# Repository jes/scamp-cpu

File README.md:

# SCAMP CPU

SCAMP is my homebrew 16-bit CPU. It stands for something like "Simple Computing and Arithmetic Microcoded Processor".

The CPU is very primitive. It doesn't support interrupts, and has no MMU, and no concept of privilege levels. It currently runs
at 1 MHz, above that the CompactFlash interface falls over. It runs a homebrew operating system, with a homebrew
programming language and compiler, and can self-host the kernel and all of the system utilities.
The environment tastes a bit like an early Unix, but works like CP/M. I used the computer to complete
almost all of [Advent of Code 2021](https://adventofcode.com/2021/).

My Advent of Code solutions are here: https://github.com/jes/aoc2021

I have some blog posts here: https://incoherency.co.uk/blog/tags/cpu.html and a web-based emulator available here: https://incoherency.co.uk/scamp/

Here are some pictures:

And here's a video with some explanation and an example session on real hardware:

## Architecture

It is a 16-bit CPU. The bus is 16-bit, registers are 16-bit, addresses are 16-bit, and memory contents are
16-bit. The upper 8 bits of an instruction select the opcode, and the lower 8 bits are available
for small immediate values. There is no support for: cache, interrupts, virtual memory, DMA, privilege rings,
floating point, and ~anything else that is not strictly necessary.

Here is a diagram of the architecture:

For more information, see [doc/UCODE.md](doc/UCODE.md) and [doc/ISA.md](doc/ISA.md).

## Try it out

The easiest way to try it out is to use the web-based emulator at https://incoherency.co.uk/scamp/

If you want to run it locally, first you'll need to build everything. Try `make -j` in the root directory of this
repository. It probably won't work on the first attempt because it works with multiple different Makefiles that have
annoying dependencies. Just run `make -j` twice or three times. If that doesn't do the trick, run `make` in `sys/` first, and then run
it in `.`. Once you get to the point that it is only complaining about `emcc`, you're done, unless you also
want to build the web-based emulator.

Having built everything, you can go into `kernel/` and start it in the emulator with `./run`:

    ~/scamp-cpu/kernel $ ./run
    make: 'os.disk' is up to date.
    SCAMP boot...
    .......................................................OK
    starting kernel...
    loading init...
          ____   ____    _    __  __ ____   __
         / ___| / ___|  / \  |  \/  |  _ \ / /__  ___
         \___ \| |     / _ \ | |\/| | |_) / / _ \/ __|
          ___) | |___ / ___ \| |  | |  __/ / (_) \__ \
         |____/ \____/_/   \_\_|  |_|_| /_/ \___/|___/

    $

If you know how to use Unix you'll probably understand how to use it. If you know how to use CP/M you'll probably
understand how it works.

If you want, you can write SLANG programs using `kilo` and compile them with `slc`. You've probably never written
SLANG before. You can learn how to use it by reading programs under `/src` (or `sys/` in the repo). It's mostly
like C but with fewer features and less safety.

## How it's made

I did these tasks, but working on several steps at a time (i.e. I didn't wait until after I had built the entire
computer before thinking about microcode or the operating system):

1. Create the CPU in Verilog, with a testbench for each part.
2. Replace the raw Verilog with Verilog that only uses 74xx-compatible primitives
   (e.g. https://github.com/TimRudy/ice-chips-verilog), but still passes the testbenches.
3. Convert the 74xx-Verilog into KiCad schematics (by hand).
4. Order the PCBs and components, solder up the PCBs, build a card cage, build a wooden case.
5. Settle on the instruction set and write the microcode (see [doc/table.html](doc/table.html), available online at https://incoherency.co.uk/interest/table.html).
5. Write a bootloader, kernel, shell, text editor, compiler, and various system utilities.

## Next steps

I suspect the computer will never be "finished", but some things I still want to work on are:

#### Hardware

 - [ ] build a hardware multiplication card (and maybe division?)
 - [ ] build a hardware RNG

#### Low-level software

 - [ ] make library blob self-hosting (compile within SCAMP/os)
 - [ ] write an strace-like debugging tool
 - [ ] write a DDT-like debugging tool
 - [ ] better facility for memory profiling (mainly to stop kilo and asm from running out of memory on large inputs)
 - [ ] atexit()
 - [ ] static initialisation of globals from constants (e.g. `var x = 5` at global scope should not take any code to initialise)
 - [ ] "const" variables (e.g. `const x = 5` should lead to `x` being replaced with the constant value `5` where possible)

#### Other software

 - [ ] write a big-fixed-point arithmetic library
 - [ ] fixed-point mathematics: pow,tan,asin,acos,atan,atan2
 - [ ] write a FORTH implementation (should it run on bare metal or under SCAMP/os?)
 - [ ] write a Z-machine interpreter and port some text adventures
 - [ ] write some games (pong? breakout? tetris?)

If you happen to want to work on any of the above, I'd be happy to help you!

## Resources

I thoroughly recommend the Nand2Tetris course. https://nand2tetris.org/

If you want to do the exercises from Nand2Tetris without learning what a hardware-description language
is, and without going through all the lectures, you can play https://nandgame.com/

Ben Eater's [videos on 8-bit CPU design](https://www.youtube.com/watch?v=HyznrdDSSGM&list=PLowKtXNTBypGqImE405J2565dvjafglHU) are excellent and heavily influenced
the design of my CPU.

I found the [YouTube playlist](https://www.youtube.com/playlist?list=PLOech0kWpH8-njQpmSNGSiQBPUvl8v3IM) for Nicolas Laurent's [compiler class](https://norswap.com/compilers/) quite helpful
in writing the parser for the compiler.

The [Build Your Own Text Editor](https://viewsourcecode.org/snaptoken/kilo/) is a fantastic tutorial that walks you through implementing
[antirez](https://github.com/antirez)'s [kilo](https://github.com/antirez/kilo) editor.

[Balazs Markus](https://github.com/bazsimarkus)'s [8250 UART example](https://github.com/bazsimarkus/Simple-8250-UART-System-with-Arduino) is helpful.

Daniel Tufvesson has a post that is a good starting point for understanding the [8-bit CompactFlash interface](http://www.waveguide.se/?article=8-bit-compact-flash-interface).

[PickledDog](https://github.com/PickledDog) has a description of an [improvement to the RC2014 CompactFlash card](https://github.com/PickledDog/rc-cfcard) that might be helpful. Also [Bill Shen's comment on the RC2014 mailing list](https://groups.google.com/g/rc2014-z80/c/LmvGa6PZNhQ/m/H8jrbp86AQAJ).

Michał Cierniak has a good blog post about [CompactFlash + 8255 interface card](https://ciernioo.wordpress.com/2015/02/10/compact-flash-8255-interface-card/) with lots
of detail on how his CompactFlash interface works.

[James Sharman](https://www.youtube.com/c/weirdboyjim) is building an interesting 8-bit pipelined CPU, and has good videos with lots of explanation on how it works.

SCAMP is featured on the [Homebrew CPU ring](https://www.homebrewcpuring.org/) which also features many other interesting homebrew CPU designs.

## Contact

You can email me on [james@incoherency.co.uk](mailto:james@incoherency.co.uk)
or read my blog: [https://incoherency.co.uk/].

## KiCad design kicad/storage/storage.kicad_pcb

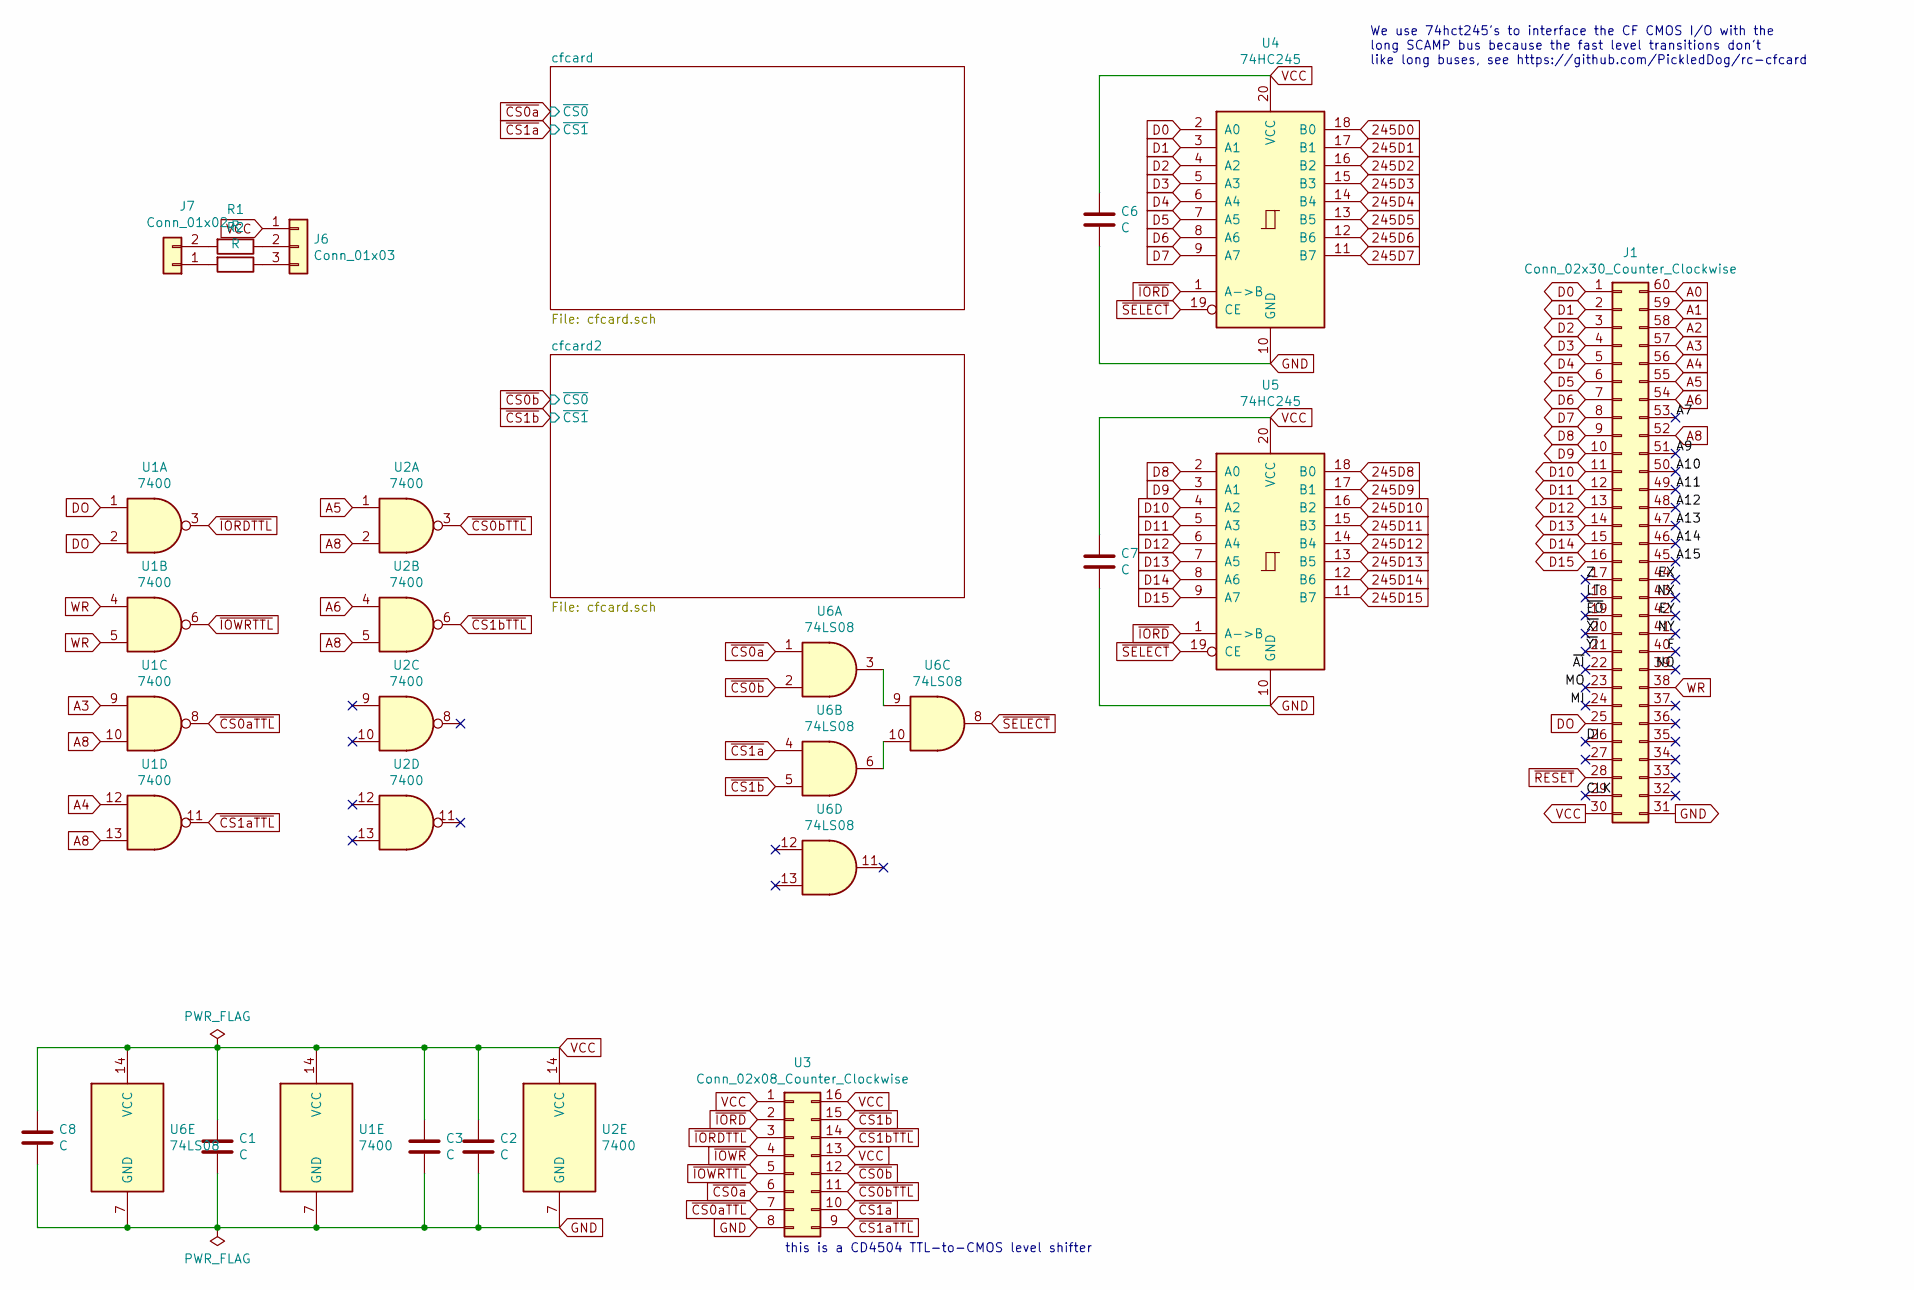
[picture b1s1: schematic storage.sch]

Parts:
C1, C2, C3, C6, C7, C8: C; C_Disc_D6.0mm_W2.5mm_P5.00mm
J1: Conn_02x30_Counter_Clockwise; PinSocket_2x30_P2.54mm_Horizontal
J6: Conn_01x03; PinHeader_1x03_P2.54mm_Vertical
J7: Conn_01x02; PinHeader_1x02_P2.54mm_Vertical
R1, R2: R; R_Axial_DIN0207_L6.3mm_D2.5mm_P10.16mm_Horizontal
U1, U2: 7400; DIP-14_W7.62mm_Socket
U3: Conn_02x08_Counter_Clockwise; DIP-16_W7.62mm_Socket
U4, U5: 74HC245; DIP-20_W7.62mm_Socket
U6: 74LS08; DIP-14_W7.62mm_Socket

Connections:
245D0: U4.18 (B0); also elsewhere on the board
245D1: U4.17 (B1); also elsewhere on the board
245D2: U4.16 (B2); also elsewhere on the board
245D3: U4.15 (B3); also elsewhere on the board
245D4: U4.14 (B4); also elsewhere on the board
245D5: U4.13 (B5); also elsewhere on the board
245D6: U4.12 (B6); also elsewhere on the board
245D7: U4.11 (B7); also elsewhere on the board
245D8: U5.18 (B0); also elsewhere on the board
245D9: U5.17 (B1); also elsewhere on the board
245D10: U5.16 (B2); also elsewhere on the board
245D11: U5.15 (B3); also elsewhere on the board
245D12: U5.14 (B4); also elsewhere on the board
245D13: U5.13 (B5); also elsewhere on the board
245D14: U5.12 (B6); also elsewhere on the board
245D15: U5.11 (B7); also elsewhere on the board
/A7: J1.53
/A9: J1.51
/A10: J1.50
/A11: J1.49
/A12: J1.48
/A13: J1.47
/A14: J1.46
/A15: J1.45
/CLK: J1.29
/DI: J1.26
/EX: J1.44
/EY: J1.42
/F: J1.40
/LT: J1.18
/MI: J1.24
/MO: J1.23
/NO: J1.39
/NX: J1.43
/NY: J1.41
/Z: J1.17
/~AI~: J1.22
/~EO~: J1.19
/~XI~: J1.20
/~YI~: J1.21
A0: J1.60; also elsewhere on the board
A1: J1.59; also elsewhere on the board
A2: J1.58; also elsewhere on the board
A3: J1.57, U1.9
A4: J1.56, U1.12
A5: J1.55, U2.1
A6: J1.54, U2.4
A8: J1.52, U1.10, U1.13, U2.2, U2.5
D0: J1.1, U4.2 (A0)
D1: J1.2, U4.3 (A1)
D2: J1.3, U4.4 (A2)
D3: J1.4, U4.5 (A3)
D4: J1.5, U4.6 (A4)
D5: J1.6, U4.7 (A5)
D6: J1.7, U4.8 (A6)
D7: J1.8, U4.9 (A7)
D8: J1.9, U5.2 (A0)
D9: J1.10, U5.3 (A1)
D10: J1.11, U5.4 (A2)
D11: J1.12, U5.5 (A3)
D12: J1.13, U5.6 (A4)
D13: J1.14, U5.7 (A5)
D14: J1.15, U5.8 (A6)
D15: J1.16, U5.9 (A7)
DO: J1.25, U1.1, U1.2
GND: C1.2, C2.2, C3.2, C6.2, C7.2, C8.2, J1.31, U1.7 (GND), U2.7 (GND), U3.8, U4.10 (GND), U5.10 (GND), U6.7 (GND); also elsewhere on the board
unnamed: J6.2, R1.1
unnamed: J6.3, R2.1
unnamed: J7.1, R2.2
unnamed: J7.2, R1.2
unnamed: U6.3, U6.9
unnamed: U6.6, U6.10
VCC: C1.1, C2.1, C3.1, C6.1, C7.1, C8.1, J1.30, J6.1, U1.14 (VCC), U2.14 (VCC), U3.1, U3.13, U3.16, U4.20 (VCC), U5.20 (VCC), U6.14 (VCC); also elsewhere on the board
WR: J1.38, U1.4, U1.5
~CS0aTTL~: U1.8, U3.7
~CS0a~: U3.6, U6.1; also elsewhere on the board
~CS0bTTL~: U2.3, U3.11
~CS0b~: U3.12, U6.2; also elsewhere on the board
~CS1aTTL~: U1.11, U3.9
~CS1a~: U3.10, U6.4; also elsewhere on the board
~CS1bTTL~: U2.6, U3.14
~CS1b~: U3.15, U6.5; also elsewhere on the board
~IORDTTL~: U1.3, U3.3
~IORD~: U3.2, U4.1 (A->B), U5.1 (A->B); also elsewhere on the board
~IOWRTTL~: U1.6, U3.5
~IOWR~: U3.4; also elsewhere on the board
~RESET~: J1.28; also elsewhere on the board
~SELECT~: U4.19 (CE), U5.19 (CE), U6.8

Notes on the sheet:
this is a CD4504 TTL-to-CMOS level shifter
We use 74hct245's to interface the CF CMOS I/O with the long SCAMP bus because the fast level transitions don't like long buses, see https://github.com/PickledDog/rc-cfcard

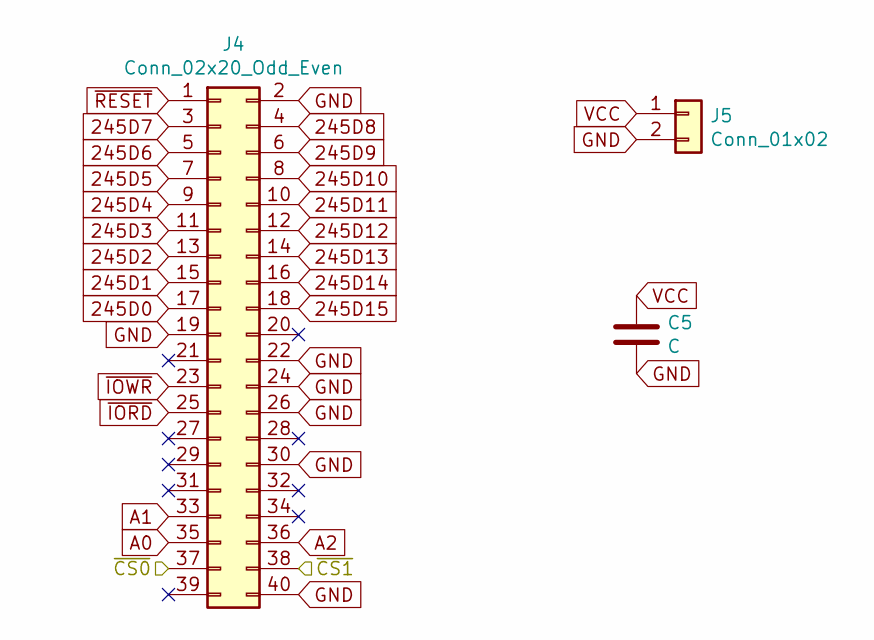
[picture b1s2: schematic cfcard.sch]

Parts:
C4: C; C_Disc_D6.0mm_W2.5mm_P5.00mm
J2: Conn_02x20_Odd_Even; cfcard
J3: Conn_01x02; PinHeader_1x02_P2.54mm_Vertical

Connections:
245D0: J2.17; also elsewhere on the board
245D1: J2.15; also elsewhere on the board
245D2: J2.13; also elsewhere on the board
245D3: J2.11; also elsewhere on the board
245D4: J2.9; also elsewhere on the board
245D5: J2.7; also elsewhere on the board
245D6: J2.5; also elsewhere on the board
245D7: J2.3; also elsewhere on the board
245D8: J2.4; also elsewhere on the board
245D9: J2.6; also elsewhere on the board
245D10: J2.8; also elsewhere on the board
245D11: J2.10; also elsewhere on the board
245D12: J2.12; also elsewhere on the board
245D13: J2.14; also elsewhere on the board
245D14: J2.16; also elsewhere on the board
245D15: J2.18; also elsewhere on the board
A0: J2.35; also elsewhere on the board
A1: J2.33; also elsewhere on the board
A2: J2.36; also elsewhere on the board
GND: C4.2, J2.2, J2.19, J2.22, J2.24, J2.26, J2.30, J2.40, J3.2; also elsewhere on the board
VCC: C4.1, J3.1; also elsewhere on the board
~CS0a~: J2.37; also elsewhere on the board
~CS1a~: J2.38; also elsewhere on the board
~IORD~: J2.25; also elsewhere on the board
~IOWR~: J2.23; also elsewhere on the board
~RESET~: J2.1; also elsewhere on the board

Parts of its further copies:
C5: C; C_Disc_D6.0mm_W2.5mm_P5.00mm
J4: Conn_02x20_Odd_Even; cfcard
J5: Conn_01x02; PinHeader_1x02_P2.54mm_Vertical

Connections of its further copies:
245D0: J4.17; also elsewhere on the board
245D1: J4.15; also elsewhere on the board
245D2: J4.13; also elsewhere on the board
245D3: J4.11; also elsewhere on the board
245D4: J4.9; also elsewhere on the board
245D5: J4.7; also elsewhere on the board
245D6: J4.5; also elsewhere on the board
245D7: J4.3; also elsewhere on the board
245D8: J4.4; also elsewhere on the board
245D9: J4.6; also elsewhere on the board
245D10: J4.8; also elsewhere on the board
245D11: J4.10; also elsewhere on the board
245D12: J4.12; also elsewhere on the board
245D13: J4.14; also elsewhere on the board
245D14: J4.16; also elsewhere on the board
245D15: J4.18; also elsewhere on the board
A0: J4.35; also elsewhere on the board
A1: J4.33; also elsewhere on the board
A2: J4.36; also elsewhere on the board
GND: C5.2, J4.2, J4.19, J4.22, J4.24, J4.26, J4.30, J4.40, J5.2; also elsewhere on the board
VCC: C5.1, J5.1; also elsewhere on the board
~CS0b~: J4.37; also elsewhere on the board
~CS1b~: J4.38; also elsewhere on the board
~IORD~: J4.25; also elsewhere on the board
~IOWR~: J4.23; also elsewhere on the board
~RESET~: J4.1; also elsewhere on the board

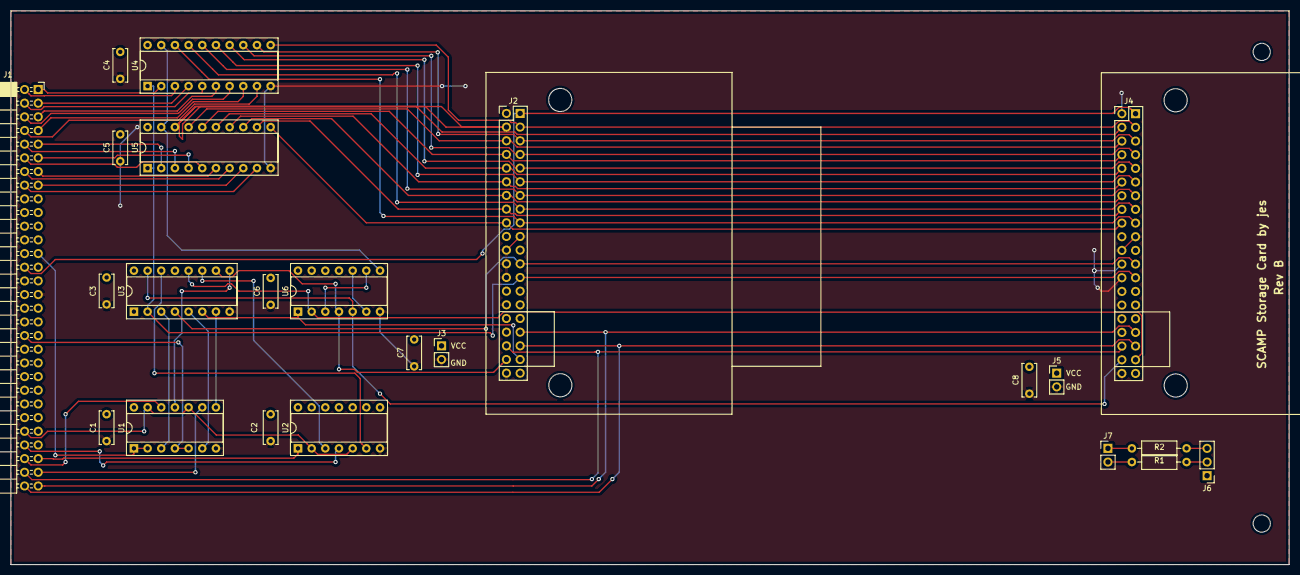
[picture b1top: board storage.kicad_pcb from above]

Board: 2 copper layers, 237.5 x 102.9 mm, 23 parts (0 on the bottom side), 64 nets.

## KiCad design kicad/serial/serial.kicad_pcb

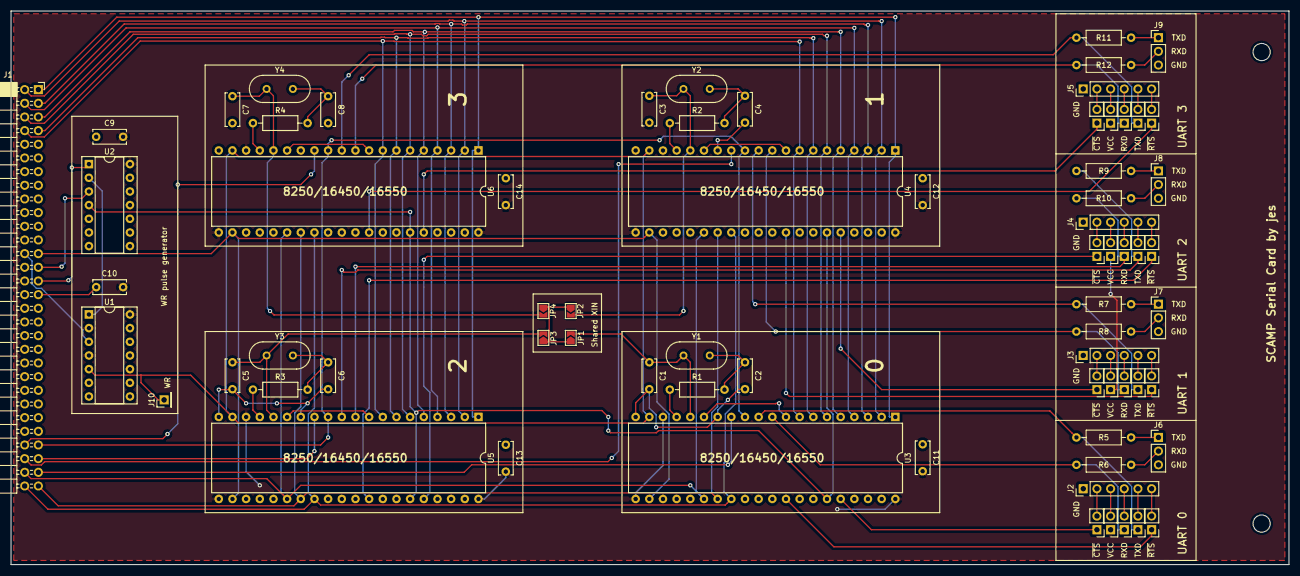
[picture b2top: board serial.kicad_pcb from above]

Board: 2 copper layers, 237.5 x 102.9 mm, 62 parts (0 on the bottom side), 70 nets.

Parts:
C1, C2, C3, C4, C5, C6, C7, C8, C9, C10, C11, C12, C13, C14: C; C_Disc_D6.0mm_W2.5mm_P5.00mm
J1: Conn_02x30_Counter_Clockwise; PinSocket_2x30_P2.54mm_Horizontal
J2, J3, J4, J5: Conn_01x06_Male; PinHeader_1x06_P2.54mm_Vertical
J6, J7, J8, J9: Conn_01x03_Male; PinHeader_1x03_P2.54mm_Vertical
J10: Conn_01x01_Male; PinHeader_1x01_P2.54mm_Vertical
JP1, JP2, JP3, JP4: SolderJumper_2_Open; SolderJumper-2_P1.3mm_Open_TrianglePad1.0x1.5mm
R1, R2, R3, R4, R5, R6, R7, R8, R9, R10, R11, R12: R; R_Axial_DIN0207_L6.3mm_D2.5mm_P10.16mm_Horizontal
RXD: Jumper_NO_Small; PinHeader_1x02_P2.54mm_Vertical
RXD#2, RXD#3, RXD#4: Jumper_NO_Small; PinHeader_1x02_P2.54mm_Vertical
TXD: Jumper_NO_Small; PinHeader_1x02_P2.54mm_Vertical
TXD#2, TXD#3, TXD#4: Jumper_NO_Small; PinHeader_1x02_P2.54mm_Vertical
U1: 74LS74; DIP-14_W7.62mm_Socket
U2: 74LS04; DIP-14_W7.62mm_Socket
U3, U4, U5, U6: 8250; DIP-40_W15.24mm
VCC: Jumper_NO_Small; PinHeader_1x02_P2.54mm_Vertical
VCC#2, VCC#3, VCC#4: Jumper_NO_Small; PinHeader_1x02_P2.54mm_Vertical
Y1, Y2, Y3, Y4: Crystal; Crystal_HC49-U_Vertical

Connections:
/uart8250a/RXD: R6.2, RXD.1, U3.10
/uart8250a/TXD: R5.2, TXD.1, U3.11
/uart8250b/RXD: R8.2, RXD#2.1, U4.10
/uart8250b/TXD: R7.2, TXD#2.1, U4.11
/uart8250c/RXD: R10.2, RXD#3.1, U5.10
/uart8250c/TXD: R9.2, TXD#3.1, U5.11
/uart8250d/RXD: R12.2, RXD#4.1, U6.10
/uart8250d/TXD: R11.2, TXD#4.1, U6.11
A0: J1.60, U3.28, U4.28, U5.28, U6.28
A1: J1.59, U3.27, U4.27, U5.27, U6.27
A2: J1.58, U3.26, U4.26, U5.26, U6.26
A3: J1.57, U3.13
A4: J1.56, U4.13
A5: J1.55, U5.13
A6: J1.54, U6.13
A7: J1.53, U3.12, U4.12, U5.12, U6.12
CLK: J1.29, U2.1
D0: J1.1, U3.1, U4.1, U5.1, U6.1
D1: J1.2, U3.2, U4.2, U5.2, U6.2
D2: J1.3, U3.3, U4.3, U5.3, U6.3
D3: J1.4, U3.4, U4.4, U5.4, U6.4
D4: J1.5, U3.5, U4.5, U5.5, U6.5
D5: J1.6, U3.6, U4.6, U5.6, U6.6
D6: J1.7, U3.7, U4.7, U5.7, U6.7
D7: J1.8, U3.8, U4.8, U5.8, U6.8
DI: J1.26, U1.3
DO: J1.25, U3.22, U4.22, U5.22, U6.22
GND: C1.2, C2.2, C3.2, C4.2, C5.2, C6.2, C7.2, C8.2, C9.2, C10.2, C11.2, C12.2, C13.2, C14.2, J1.31, J2.1, J3.1, J4.1, J5.1, J6.3, J7.3, J8.3, J9.3, U1.7, U2.7, U3.14, U3.20, U3.25, U4.14, U4.20, U4.25, U5.14, U5.20, U5.25, U6.14, U6.20, U6.25
unnamed: C1.1, JP1.2, U3.16, Y1.1
unnamed: C2.1, R1.2, Y1.2
unnamed: C3.1, JP2.2, U4.16, Y2.1
unnamed: C4.1, R2.2, Y2.2
unnamed: C5.1, JP3.2, U5.16, Y3.1
unnamed: C6.1, R3.2, Y3.2
unnamed: C7.1, JP4.2, U6.16, Y4.1
unnamed: C8.1, R4.2, Y4.2
unnamed: J2.3, VCC.2
unnamed: J2.4, RXD.2
unnamed: J2.5, TXD.2
unnamed: J3.3, VCC#2.2
unnamed: J3.4, RXD#2.2
unnamed: J3.5, TXD#2.2
unnamed: J4.3, VCC#3.2
unnamed: J4.4, RXD#3.2
unnamed: J4.5, TXD#3.2
unnamed: J5.3, VCC#4.2
unnamed: J5.4, RXD#4.2
unnamed: J5.5, TXD#4.2
unnamed: J6.1, R5.1
unnamed: J6.2, R6.1
unnamed: J7.1, R7.1
unnamed: J7.2, R8.1
unnamed: J8.1, R9.1
unnamed: J8.2, R10.1
unnamed: J9.1, R11.1
unnamed: J9.2, R12.1
unnamed: R1.1, U3.17
unnamed: R2.1, U4.17
unnamed: R3.1, U5.17
unnamed: R4.1, U6.17
unnamed: U3.9, U3.15
unnamed: U4.9, U4.15
unnamed: U5.9, U5.15
unnamed: U6.9, U6.15
SHAREDXIN: JP1.1, JP2.1, JP3.1, JP4.1
VCC: C9.1, C10.1, C11.1, C12.1, C13.1, C14.1, J1.30, U1.2, U1.4, U1.14, U2.14, U3.18, U3.21, U3.40, U4.18, U4.21, U4.40, U5.18, U5.21, U5.40, U6.18, U6.21, U6.40, VCC.1, VCC#2.1, VCC#3.1, VCC#4.1
WR: J10.1, U1.5, U3.19, U4.19, U5.19, U6.19
inv_CLK: U1.1, U2.2
inv_~RESET: U2.4, U3.35, U4.35, U5.35, U6.35
~RESET: J1.27, U2.3

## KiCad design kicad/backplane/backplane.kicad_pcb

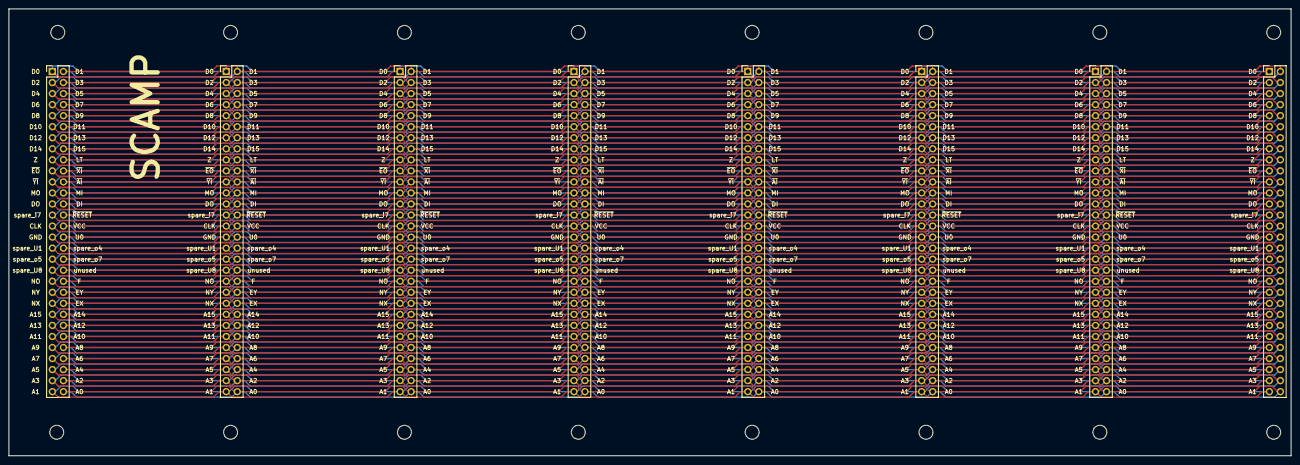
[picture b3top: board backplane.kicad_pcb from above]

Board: 2 copper layers, 295.0 x 102.8 mm, 8 parts (0 on the bottom side), 60 nets.

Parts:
J1, J2, J3, J4, J5, J6, J7, J8: Conn_02x30_Counter_Clockwise; PinHeader_2x30_P2.54mm_Vertical

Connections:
A0: J1.60, J2.60, J3.60, J4.60, J5.60, J6.60, J7.60, J8.60
A1: J1.59, J2.59, J3.59, J4.59, J5.59, J6.59, J7.59, J8.59
A2: J1.58, J2.58, J3.58, J4.58, J5.58, J6.58, J7.58, J8.58
A3: J1.57, J2.57, J3.57, J4.57, J5.57, J6.57, J7.57, J8.57
A4: J1.56, J2.56, J3.56, J4.56, J5.56, J6.56, J7.56, J8.56
A5: J1.55, J2.55, J3.55, J4.55, J5.55, J6.55, J7.55, J8.55
A6: J1.54, J2.54, J3.54, J4.54, J5.54, J6.54, J7.54, J8.54
A7: J1.53, J2.53, J3.53, J4.53, J5.53, J6.53, J7.53, J8.53
A8: J1.52, J2.52, J3.52, J4.52, J5.52, J6.52, J7.52, J8.52
A9: J1.51, J2.51, J3.51, J4.51, J5.51, J6.51, J7.51, J8.51
A10: J1.50, J2.50, J3.50, J4.50, J5.50, J6.50, J7.50, J8.50
A11: J1.49, J2.49, J3.49, J4.49, J5.49, J6.49, J7.49, J8.49
A12: J1.48, J2.48, J3.48, J4.48, J5.48, J6.48, J7.48, J8.48
A13: J1.47, J2.47, J3.47, J4.47, J5.47, J6.47, J7.47, J8.47
A14: J1.46, J2.46, J3.46, J4.46, J5.46, J6.46, J7.46, J8.46
A15: J1.45, J2.45, J3.45, J4.45, J5.45, J6.45, J7.45, J8.45
CLK: J1.29, J2.29, J3.29, J4.29, J5.29, J6.29, J7.29, J8.29
D0: J1.1, J2.1, J3.1, J4.1, J5.1, J6.1, J7.1, J8.1
D1: J1.2, J2.2, J3.2, J4.2, J5.2, J6.2, J7.2, J8.2
D2: J1.3, J2.3, J3.3, J4.3, J5.3, J6.3, J7.3, J8.3
D3: J1.4, J2.4, J3.4, J4.4, J5.4, J6.4, J7.4, J8.4
D4: J1.5, J2.5, J3.5, J4.5, J5.5, J6.5, J7.5, J8.5
D5: J1.6, J2.6, J3.6, J4.6, J5.6, J6.6, J7.6, J8.6
D6: J1.7, J2.7, J3.7, J4.7, J5.7, J6.7, J7.7, J8.7
D7: J1.8, J2.8, J3.8, J4.8, J5.8, J6.8, J7.8, J8.8
D8: J1.9, J2.9, J3.9, J4.9, J5.9, J6.9, J7.9, J8.9
D9: J1.10, J2.10, J3.10, J4.10, J5.10, J6.10, J7.10, J8.10
D10: J1.11, J2.11, J3.11, J4.11, J5.11, J6.11, J7.11, J8.11
D11: J1.12, J2.12, J3.12, J4.12, J5.12, J6.12, J7.12, J8.12
D12: J1.13, J2.13, J3.13, J4.13, J5.13, J6.13, J7.13, J8.13
D13: J1.14, J2.14, J3.14, J4.14, J5.14, J6.14, J7.14, J8.14
D14: J1.15, J2.15, J3.15, J4.15, J5.15, J6.15, J7.15, J8.15
D15: J1.16, J2.16, J3.16, J4.16, J5.16, J6.16, J7.16, J8.16
DI: J1.26, J2.26, J3.26, J4.26, J5.26, J6.26, J7.26, J8.26
DO: J1.25, J2.25, J3.25, J4.25, J5.25, J6.25, J7.25, J8.25
EX: J1.44, J2.44, J3.44, J4.44, J5.44, J6.44, J7.44, J8.44
EY: J1.42, J2.42, J3.42, J4.42, J5.42, J6.42, J7.42, J8.42
F: J1.40, J2.40, J3.40, J4.40, J5.40, J6.40, J7.40, J8.40
GND: J1.31, J2.31, J3.31, J4.31, J5.31, J6.31, J7.31, J8.31
LT: J1.18, J2.18, J3.18, J4.18, J5.18, J6.18, J7.18, J8.18
MI: J1.24, J2.24, J3.24, J4.24, J5.24, J6.24, J7.24, J8.24
MO: J1.23, J2.23, J3.23, J4.23, J5.23, J6.23, J7.23, J8.23
NO: J1.39, J2.39, J3.39, J4.39, J5.39, J6.39, J7.39, J8.39
NX: J1.43, J2.43, J3.43, J4.43, J5.43, J6.43, J7.43, J8.43
NY: J1.41, J2.41, J3.41, J4.41, J5.41, J6.41, J7.41, J8.41
U0: J1.32, J2.32, J3.32, J4.32, J5.32, J6.32, J7.32, J8.32
VCC: J1.30, J2.30, J3.30, J4.30, J5.30, J6.30, J7.30, J8.30
Z: J1.17, J2.17, J3.17, J4.17, J5.17, J6.17, J7.17, J8.17
spare_U1: J1.33, J2.33, J3.33, J4.33, J5.33, J6.33, J7.33, J8.33
spare_U8: J1.37, J2.37, J3.37, J4.37, J5.37, J6.37, J7.37, J8.37
spare_i7: J1.27, J2.27, J3.27, J4.27, J5.27, J6.27, J7.27, J8.27
spare_o4: J1.34, J2.34, J3.34, J4.34, J5.34, J6.34, J7.34, J8.34
spare_o5: J1.35, J2.35, J3.35, J4.35, J5.35, J6.35, J7.35, J8.35
spare_o7: J1.36, J2.36, J3.36, J4.36, J5.36, J6.36, J7.36, J8.36
unused: J1.38, J2.38, J3.38, J4.38, J5.38, J6.38, J7.38, J8.38
~AI~: J1.22, J2.22, J3.22, J4.22, J5.22, J6.22, J7.22, J8.22
~EO~: J1.19, J2.19, J3.19, J4.19, J5.19, J6.19, J7.19, J8.19
~RESET~: J1.28, J2.28, J3.28, J4.28, J5.28, J6.28, J7.28, J8.28
~XI~: J1.20, J2.20, J3.20, J4.20, J5.20, J6.20, J7.20, J8.20
~YI~: J1.21, J2.21, J3.21, J4.21, J5.21, J6.21, J7.21, J8.21

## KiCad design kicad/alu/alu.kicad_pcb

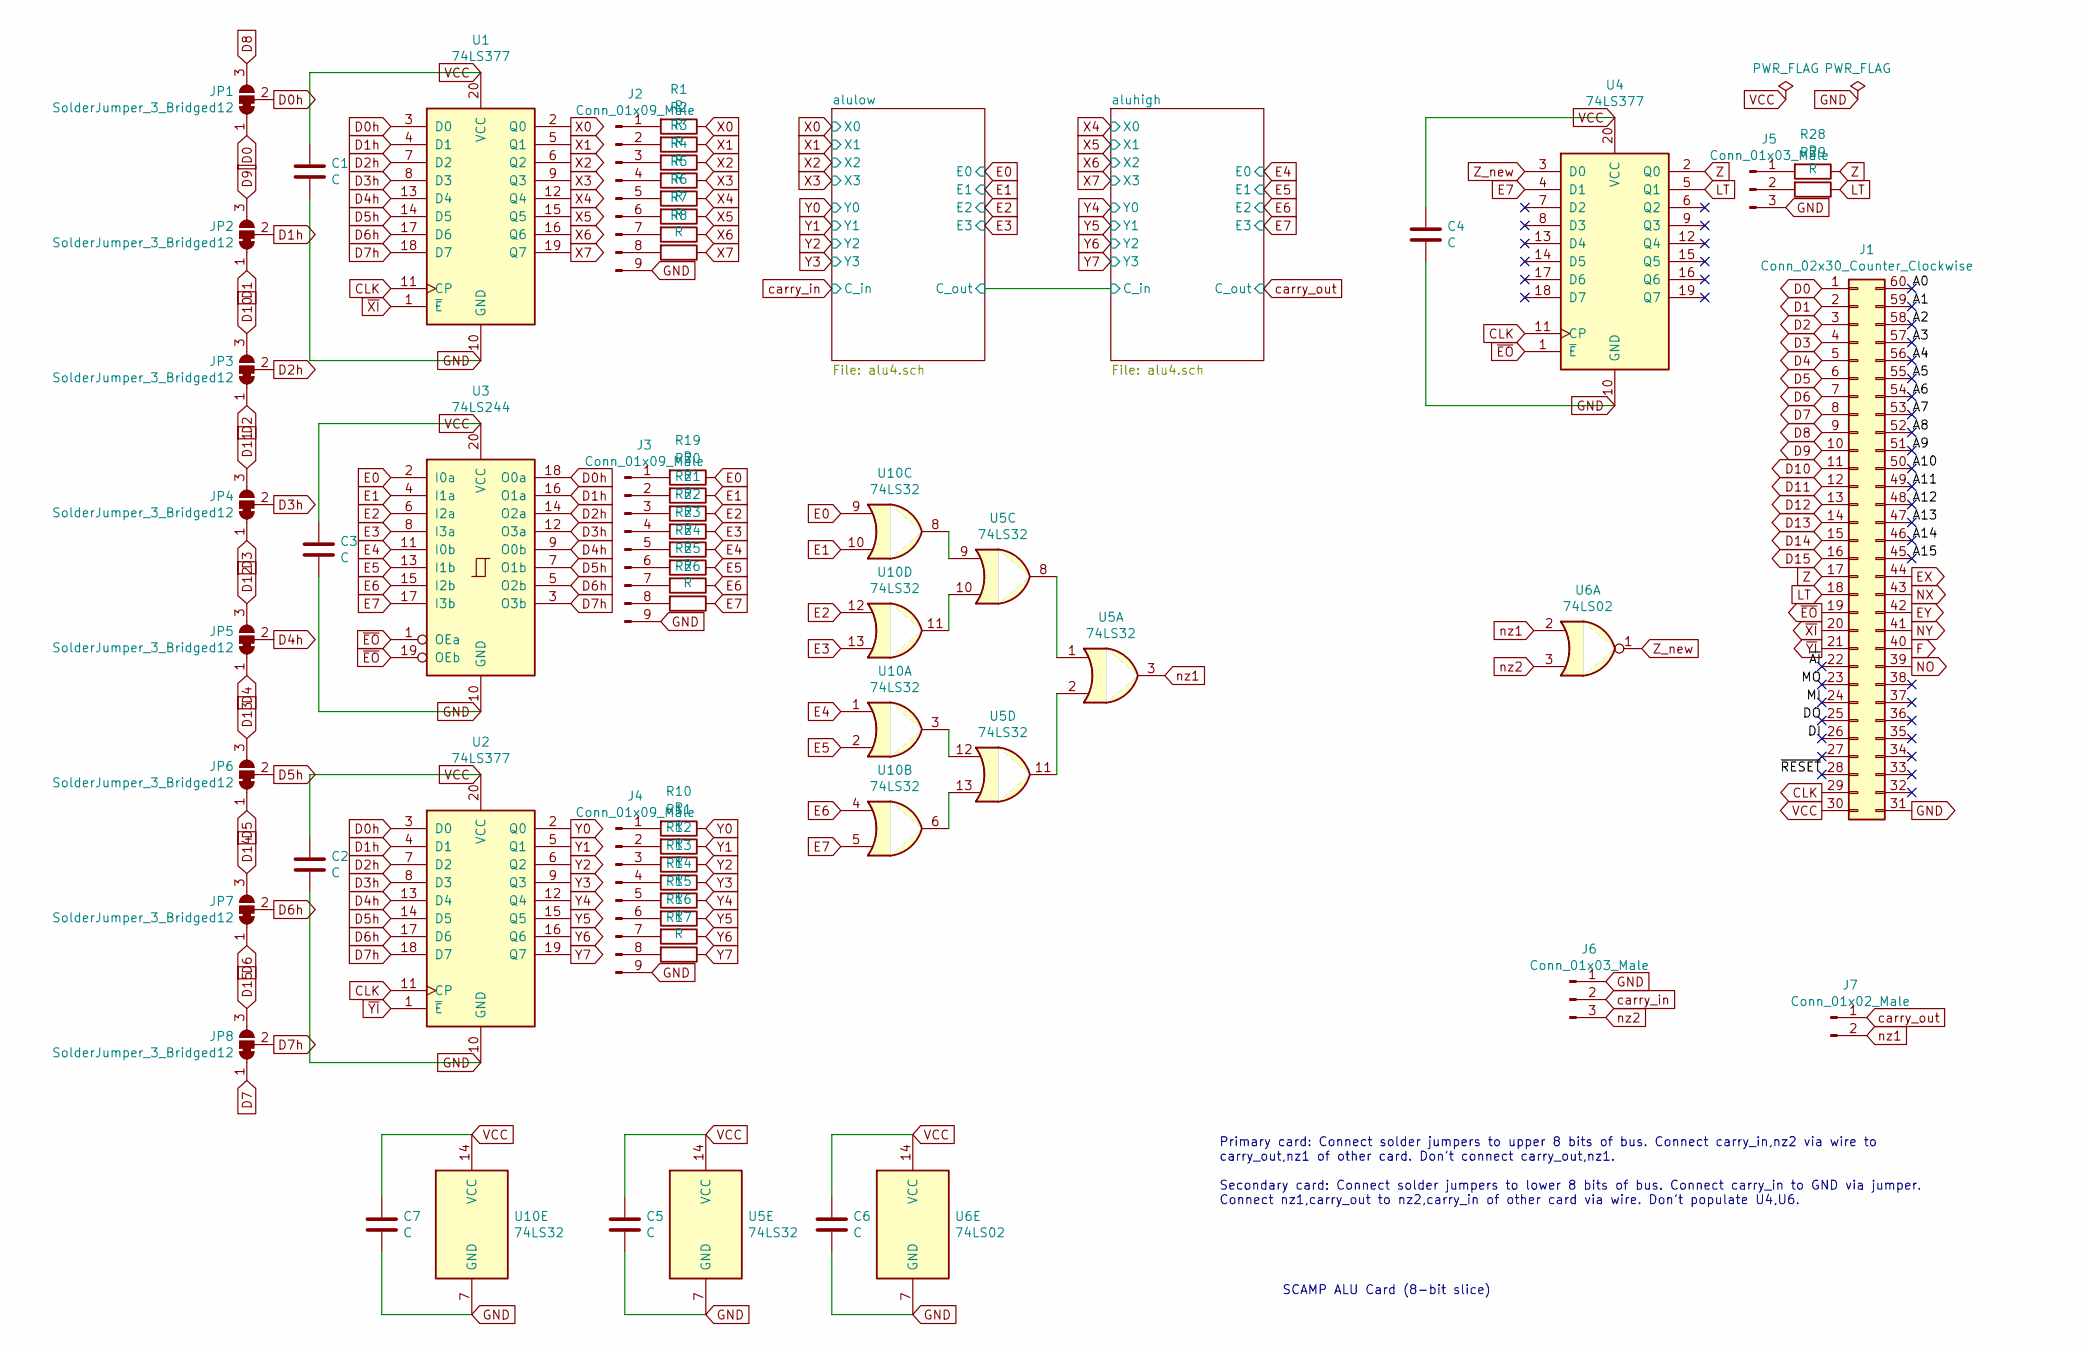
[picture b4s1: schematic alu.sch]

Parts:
C1, C2, C3, C4, C5, C6, C7: C; C_Disc_D5.0mm_W2.5mm_P2.50mm
J1: Conn_02x30_Counter_Clockwise; PinSocket_2x30_P2.54mm_Horizontal
J2, J3, J4: Conn_01x09_Male; PinHeader_1x09_P2.54mm_Vertical
J5, J6: Conn_01x03_Male; PinHeader_1x03_P2.54mm_Vertical
J7: Conn_01x02_Male; PinHeader_1x02_P2.54mm_Vertical
JP1, JP2, JP3, JP4, JP5, JP6, JP7, JP8: SolderJumper_3_Bridged12; SolderJumper-3_P1.3mm_Open_Pad1.0x1.5mm
R1, R2, R3, R4, R5, R6, R7, R8, R10, R11, R12, R13, R14, R15, R16, R17, R19, R20, R21, R22, R23, R24, R25, R26, R28, R29: R; R_Axial_DIN0207_L6.3mm_D2.5mm_P7.62mm_Horizontal
U1, U2, U4: 74LS377; DIP-20_W7.62mm_Socket
U3: 74LS244; DIP-20_W7.62mm_Socket
U5, U10: 74LS32; DIP-14_W7.62mm_Socket
U6: 74LS02; DIP-14_W7.62mm_Socket

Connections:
/A0: J1.60
/A1: J1.59
/A2: J1.58
/A3: J1.57
/A4: J1.56
/A5: J1.55
/A6: J1.54
/A7: J1.53
/A8: J1.52
/A9: J1.51
/A10: J1.50
/A11: J1.49
/A12: J1.48
/A13: J1.47
/A14: J1.46
/A15: J1.45
/DI: J1.26
/DO: J1.25
/MI: J1.24
/MO: J1.23
/~AI~: J1.22
/~RESET~: J1.28
CLK: J1.29, U1.11 (CP), U2.11 (CP), U4.11 (CP)
D0: J1.1, JP1.1 (A)
D0h: JP1.2 (C), U1.3 (D0), U2.3 (D0), U3.18 (O0a)
D1: J1.2, JP2.1 (A)
D1h: JP2.2 (C), U1.4 (D1), U2.4 (D1), U3.16 (O1a)
D2: J1.3, JP3.1 (A)
D2h: JP3.2 (C), U1.7 (D2), U2.7 (D2), U3.14 (O2a)
D3: J1.4, JP4.1 (A)
D3h: JP4.2 (C), U1.8 (D3), U2.8 (D3), U3.12 (O3a)
D4: J1.5, JP5.1 (A)
D4h: JP5.2 (C), U1.13 (D4), U2.13 (D4), U3.9 (O0b)
D5: J1.6, JP6.1 (A)
D5h: JP6.2 (C), U1.14 (D5), U2.14 (D5), U3.7 (O1b)
D6: J1.7, JP7.1 (A)
D6h: JP7.2 (C), U1.17 (D6), U2.17 (D6), U3.5 (O2b)
D7: J1.8, JP8.1 (A)
D7h: JP8.2 (C), U1.18 (D7), U2.18 (D7), U3.3 (O3b)
D8: J1.9, JP1.3 (B)
D9: J1.10, JP2.3 (B)
D10: J1.11, JP3.3 (B)
D11: J1.12, JP4.3 (B)
D12: J1.13, JP5.3 (B)
D13: J1.14, JP6.3 (B)
D14: J1.15, JP7.3 (B)
D15: J1.16, JP8.3 (B)
E0: R19.1, U3.2 (I0a), U10.9; also elsewhere on the board
E1: R20.1, U3.4 (I1a), U10.10; also elsewhere on the board
E2: R21.1, U3.6 (I2a), U10.12; also elsewhere on the board
E3: R22.1, U3.8 (I3a), U10.13; also elsewhere on the board
E4: R23.1, U3.11 (I0b), U10.1; also elsewhere on the board
E5: R24.1, U3.13 (I1b), U10.2; also elsewhere on the board
E6: R25.1, U3.15 (I2b), U10.4; also elsewhere on the board
E7: R26.1, U3.17 (I3b), U4.4 (D1), U10.5; also elsewhere on the board
EX: J1.44; also elsewhere on the board
EY: J1.42; also elsewhere on the board
F: J1.40; also elsewhere on the board
GND: C1.2, C2.2, C3.2, C4.2, C5.2, C6.2, C7.2, J1.31, J2.9, J3.9, J4.9, J5.3, J6.1, U1.10 (GND), U2.10 (GND), U3.10 (GND), U4.10 (GND), U5.7 (GND), U6.7 (GND), U10.7 (GND); also elsewhere on the board
LT: J1.18, R29.1, U4.5 (Q1)
NO: J1.39; also elsewhere on the board
NX: J1.43; also elsewhere on the board
NY: J1.41; also elsewhere on the board
unnamed: J2.1, R1.2
unnamed: J2.2, R2.2
unnamed: J2.3, R3.2
unnamed: J2.4, R4.2
unnamed: J2.5, R5.2
unnamed: J2.6, R6.2
unnamed: J2.7, R7.2
unnamed: J2.8, R8.2
unnamed: J3.1, R19.2
unnamed: J3.2, R20.2
unnamed: J3.3, R21.2
unnamed: J3.4, R22.2
unnamed: J3.5, R23.2
unnamed: J3.6, R24.2
unnamed: J3.7, R25.2
unnamed: J3.8, R26.2
unnamed: J4.1, R10.2
unnamed: J4.2, R11.2
unnamed: J4.3, R12.2
unnamed: J4.4, R13.2
unnamed: J4.5, R14.2
unnamed: J4.6, R15.2
unnamed: J4.7, R16.2
unnamed: J4.8, R17.2
unnamed: J5.1, R28.2
unnamed: J5.2, R29.2
unnamed: U5.1, U5.8
unnamed: U5.2, U5.11
unnamed: U5.12, U10.3
unnamed: U5.13, U10.6
unnamed: U5.9, U10.8
unnamed: U5.10, U10.11
VCC: C1.1, C2.1, C3.1, C4.1, C5.1, C6.1, C7.1, J1.30, U1.20 (VCC), U2.20 (VCC), U3.20 (VCC), U4.20 (VCC), U5.14 (VCC), U6.14 (VCC), U10.14 (VCC); also elsewhere on the board
X0: R1.1, U1.2 (Q0); also elsewhere on the board
X1: R2.1, U1.5 (Q1); also elsewhere on the board
X2: R3.1, U1.6 (Q2); also elsewhere on the board
X3: R4.1, U1.9 (Q3); also elsewhere on the board
X4: R5.1, U1.12 (Q4); also elsewhere on the board
X5: R6.1, U1.15 (Q5); also elsewhere on the board
X6: R7.1, U1.16 (Q6); also elsewhere on the board
X7: R8.1, U1.19 (Q7); also elsewhere on the board
Y0: R10.1, U2.2 (Q0); also elsewhere on the board
Y1: R11.1, U2.5 (Q1); also elsewhere on the board
Y2: R12.1, U2.6 (Q2); also elsewhere on the board
Y3: R13.1, U2.9 (Q3); also elsewhere on the board
Y4: R14.1, U2.12 (Q4); also elsewhere on the board
Y5: R15.1, U2.15 (Q5); also elsewhere on the board
Y6: R16.1, U2.16 (Q6); also elsewhere on the board
Y7: R17.1, U2.19 (Q7); also elsewhere on the board
Z: J1.17, R28.1, U4.2 (Q0)
Z_new: U4.3 (D0), U6.1
carry_in: J6.2; also elsewhere on the board
carry_out: J7.1; also elsewhere on the board
nz1: J7.2, U5.3, U6.2
nz2: J6.3, U6.3
~EO~: J1.19, U3.1 (OEa), U3.19 (OEb), U4.1 (~E)
~XI~: J1.20, U1.1 (~E)
~YI~: J1.21, U2.1 (~E)

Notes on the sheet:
SCAMP ALU Card (8-bit slice)
Primary card: Connect solder jumpers to upper 8 bits of bus. Connect carry_in,nz2 via wire to carry_out,nz1 of other card. Don't connect carry_out,nz1. Secondary card: Connect solder jumpers to lower 8 bits of bus. Connect carry_in to GND via jumper. Connect nz1,carry_out to nz2,carry_in of other c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
